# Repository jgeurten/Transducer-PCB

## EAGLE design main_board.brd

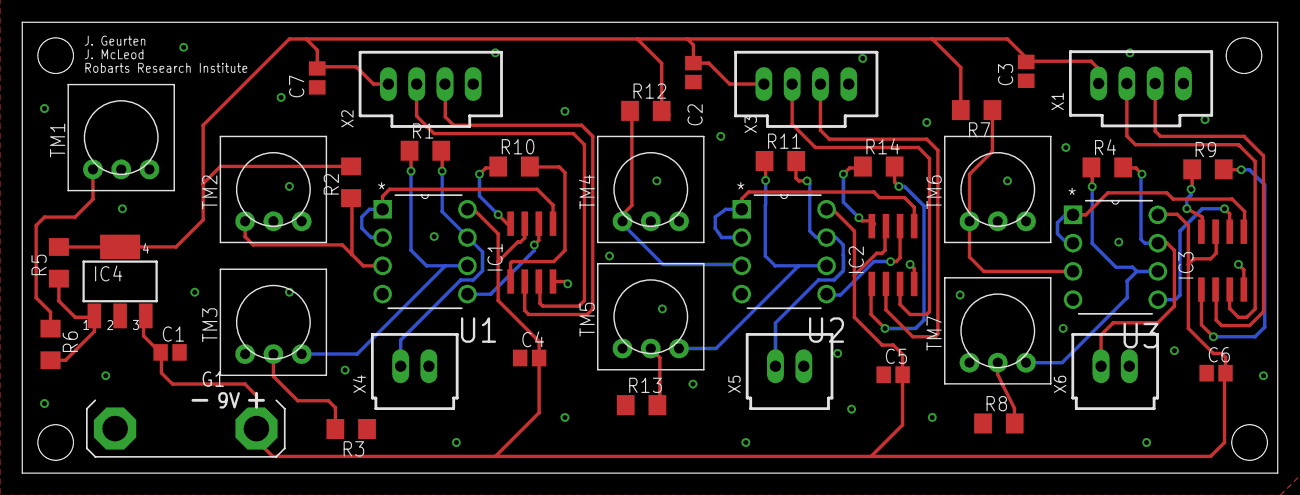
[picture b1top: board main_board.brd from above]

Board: 2 copper layers, 112.8 x 40.5 mm, 42 parts (0 on the bottom side), 35 nets.

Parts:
C1: 1uF; C2012
C2, C3, C4, C5, C6, C7: 10uF; C2012
G1: AB9V
IC1, IC2, IC3: LT1168ACS8; SOIC8
IC4: 317EMP; SOT223
R1, R4: 10kO; R1206
R2, R7, R12: 30kO; R1206
R3, R8, R13: 2kO; R1206
R5: 1KO; R1206
R6: 4kO; R1206
R9, R14: 110 ohm; R1206
R10: 110ohm; R1206
R11: 10kO\; R1206
TM1, TM2, TM3, TM4, TM5, TM6, TM7: TRIM-3386
U1, U2, U3: TLC272IP; DIP254P762X508-8
X1, X2, X3: C-GRID-04-70543; 70543-04
X4, X5, X6: C-GRID-02-70543; 70543-02

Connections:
ADJ: IC4.1, R5.1, R6.2
BLUE_IN_B: IC3.3, X1.2
BLUE_IN_R: IC3.2, X1.3
GND: C1.2, C2.2, C3.2, C4.1, C5.1, C6.1, C7.2, G1.-, IC1.4, IC2.4, IC3.4, R3.1, R8.1, R13.1, TM1.2, TM2.2, TM4.2, TM6.2, U1.4, U2.4, U3.4, X1.4, X2.4, X3.4, X4.2, X5.2, X6.2
GREEN_IN_B: IC1.3, X2.2
GREEN_IN_R: IC1.2, X2.3
IC3_RG1: IC3.1, R9.2
IC3_RG8: IC3.8, R9.1
unnamed: R6.1, TM1.1
unnamed: IC1.1, R10.2
unnamed: IC1.8, R10.1
unnamed: IC2.1, R14.2
unnamed: IC2.8, R14.1
TM2POT2: R3.2, TM3.2
TM5POT2: R13.2, TM5.2
TM7POT2: R8.2, TM7.2
U1_1IN+: R2.1, TM2.1, U1.3
U1_1IN-: IC1.5, U1.1, U1.2
U1_2IN+: IC1.6, U1.5
U1_2IN-: R1.1, TM3.3, U1.6
U1_2OUT: R1.2, U1.7, X4.1
U2_1IN+: R12.1, TM4.1, U2.3
U2_1IN-: IC2.5, U2.1, U2.2
U2_2IN+: IC2.6, U2.5
U2_2IN-: R11.1, TM5.3, U2.6
U2_2OUT: R11.2, U2.7, X5.1
U3_1_IN+: R7.1, TM6.1, U3.3
U3_1_IN-: IC3.5, U3.1, U3.2
U3_2OUT: R4.2, U3.7, X6.1
U3_2_IN+: IC3.6, U3.5
U3_2_IN-: R4.1, TM7.3, U3.6
VCC: C1.1, C4.2, C5.2, C6.2, G1.+, IC1.7, IC2.7, IC3.7, IC4.3, U1.8, U2.8, U3.8
VDD: C2.1, C3.1, C7.1, IC4.4, R2.2, R5.2, R7.2, R12.2, X1.1, X2.1, X3.1
WHITE_IN_B: IC2.3, X3.2
WHITE_IN_R: IC2.2, X3.3

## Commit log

2017-08-10 Updated entire repo. Intitial commit with new folder
2017-08-10 Added bill of materials
2017-08-13 Updated via positions
2017-08-13 Better layout
2017-08-13 Added stuff
2017-08-13 Connections made
2017-08-13 Re-doing main board. Use this
2017-08-13 Progress
2017-08-13 Board is 100%. Left to do: text
2017-08-14 Edited text on board.
2017-08-15 Merging
2017-08-16 Finished board
2017-08-22 Finished board. No errors remaining.
2017-08-22 Cleaned up repo
2017-08-22 Finished.
2017-08-22 Added female connectors to BOM
